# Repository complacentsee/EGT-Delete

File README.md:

View this project on [CADLAB.io](https://cadlab.io/project/1122). 

# EGT-Delete

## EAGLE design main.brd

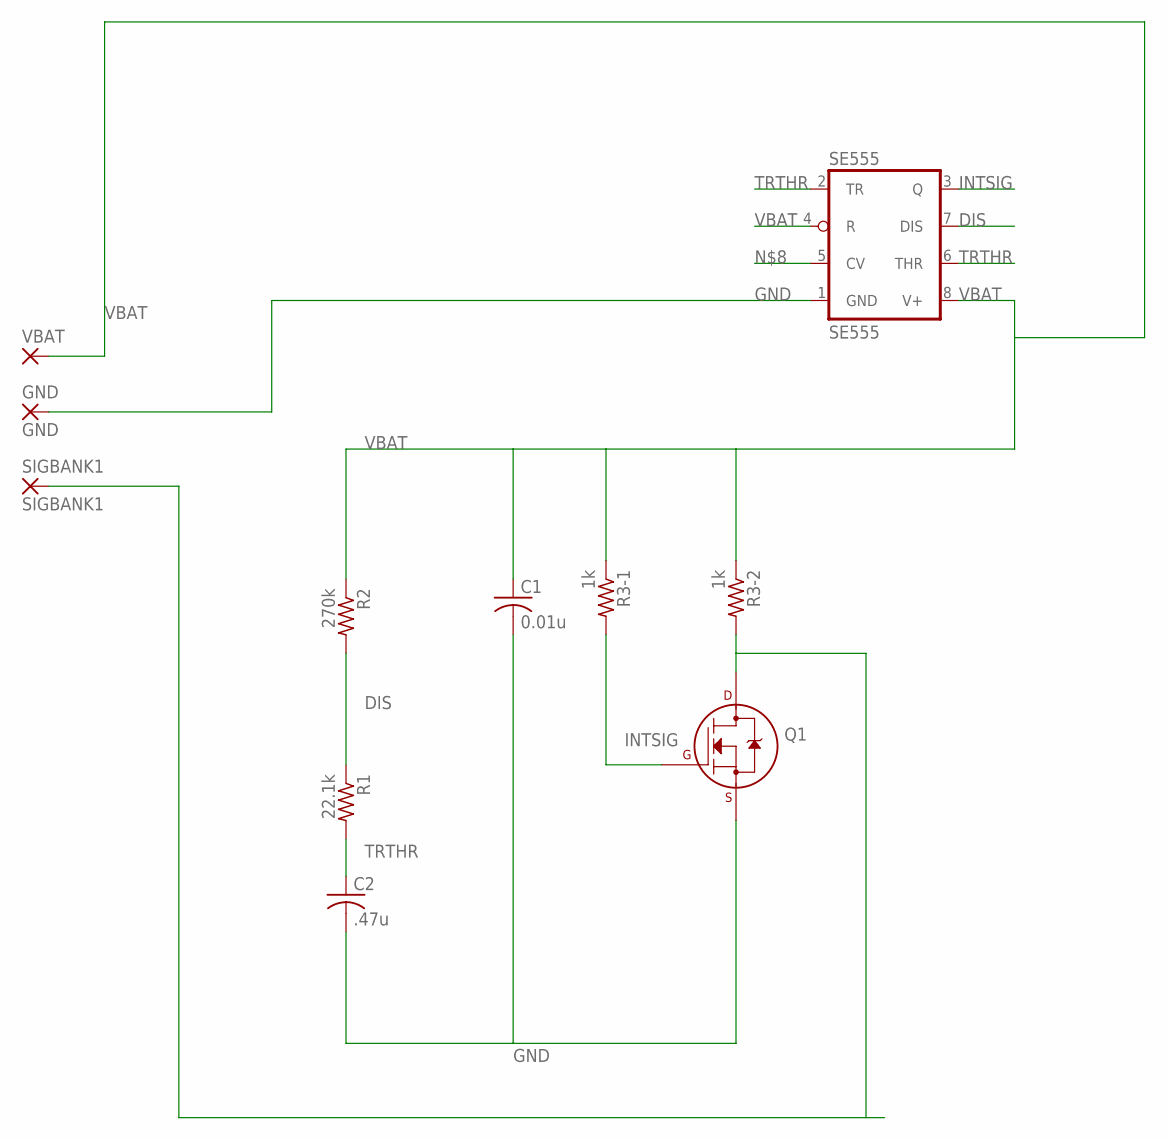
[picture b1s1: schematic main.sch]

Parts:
C1: 0.01u; C0805
C2: .47u; C0805
GND: GND; 3,17/1,3
Q1: 2N7002_SOT23; SOT-23
R1: 22.1k; R0805
R2: 270k; R0805
R3-1, R3-2: 1k; R0805
SE555: SE555; SO08
SIGBANK1: SIGBANK1; 3,17/1,3
VBAT: 3,17/1,3

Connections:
DIS: R1.1, R2.2, SE555.7 (DIS)
GND: C1.2, C2.2, GND.1, Q1.2 (S), SE555.1 (GND)
INTSIG: Q1.1 (G), R3-1.2, SE555.3 (Q)
SIGBANK1: Q1.3 (D), R3-2.2, SIGBANK1.1
TRTHR: C2.1, R1.2, SE555.2 (TR), SE555.6 (THR)
VBAT: C1.1, R2.1, R3-1.1, R3-2.1, SE555.4 (R), SE555.8 (V+), VBAT.1

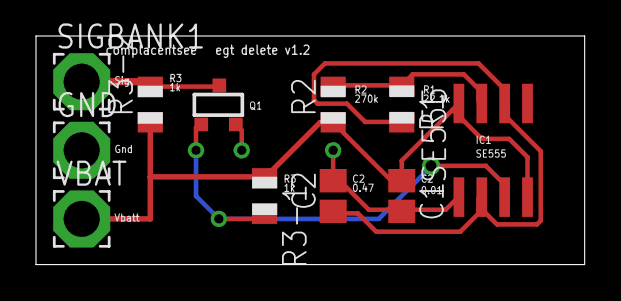
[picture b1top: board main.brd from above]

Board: 2 copper layers, 30.5 x 12.7 mm, 11 parts (0 on the bottom side), 6 nets.

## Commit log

2014-11-15 :lollipop: Added .gitattributes & .gitignore files
2014-11-15 EGT Delete
    Version 1.2
2014-11-15 Corrections for pads
2014-11-15 Added BOM and submission package.
2018-06-02 Backlink to CADLAB.io has been added.
